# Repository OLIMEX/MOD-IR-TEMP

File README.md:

# MOD-IR-TEMP
MOD-IR-TEMP is non contact high precision temperature measurement module with I2C/UEXT interface

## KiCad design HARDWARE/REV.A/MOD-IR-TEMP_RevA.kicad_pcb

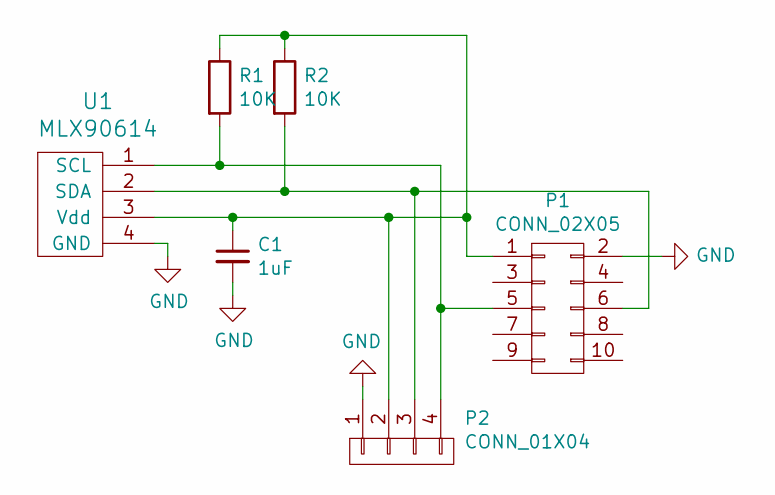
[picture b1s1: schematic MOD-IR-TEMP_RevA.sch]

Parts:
C1: 1uF
P1: CONN_02X05
P2: CONN_01X04
R1, R2: 10K
U1: MLX90614

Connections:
GND: C1.2, P1.2, P2.1, U1.4 (GND)
unnamed: C1.1, P1.1, P2.2, R1.1, R2.1, U1.3 (Vdd)
unnamed: P1.5, P2.4, R1.2, U1.1 (SCL)
unnamed: P1.6, P2.3, R2.2, U1.2 (SDA)

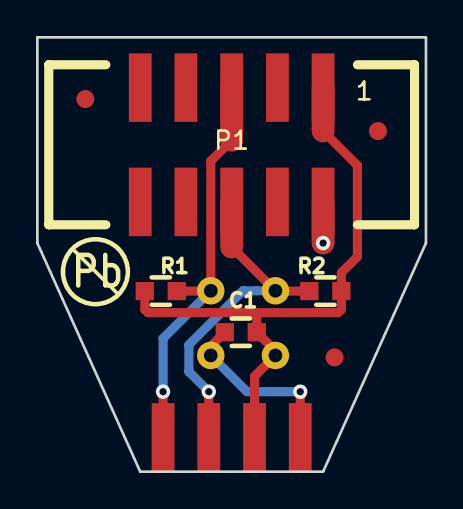
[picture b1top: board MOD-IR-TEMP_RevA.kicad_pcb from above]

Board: 2 copper layers, 21.6 x 24.1 mm, 6 parts (1 on the bottom side), 4 nets.

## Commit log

2018-03-23 upload CAD files and demo software
2018-03-23 update arduino sketch with library
